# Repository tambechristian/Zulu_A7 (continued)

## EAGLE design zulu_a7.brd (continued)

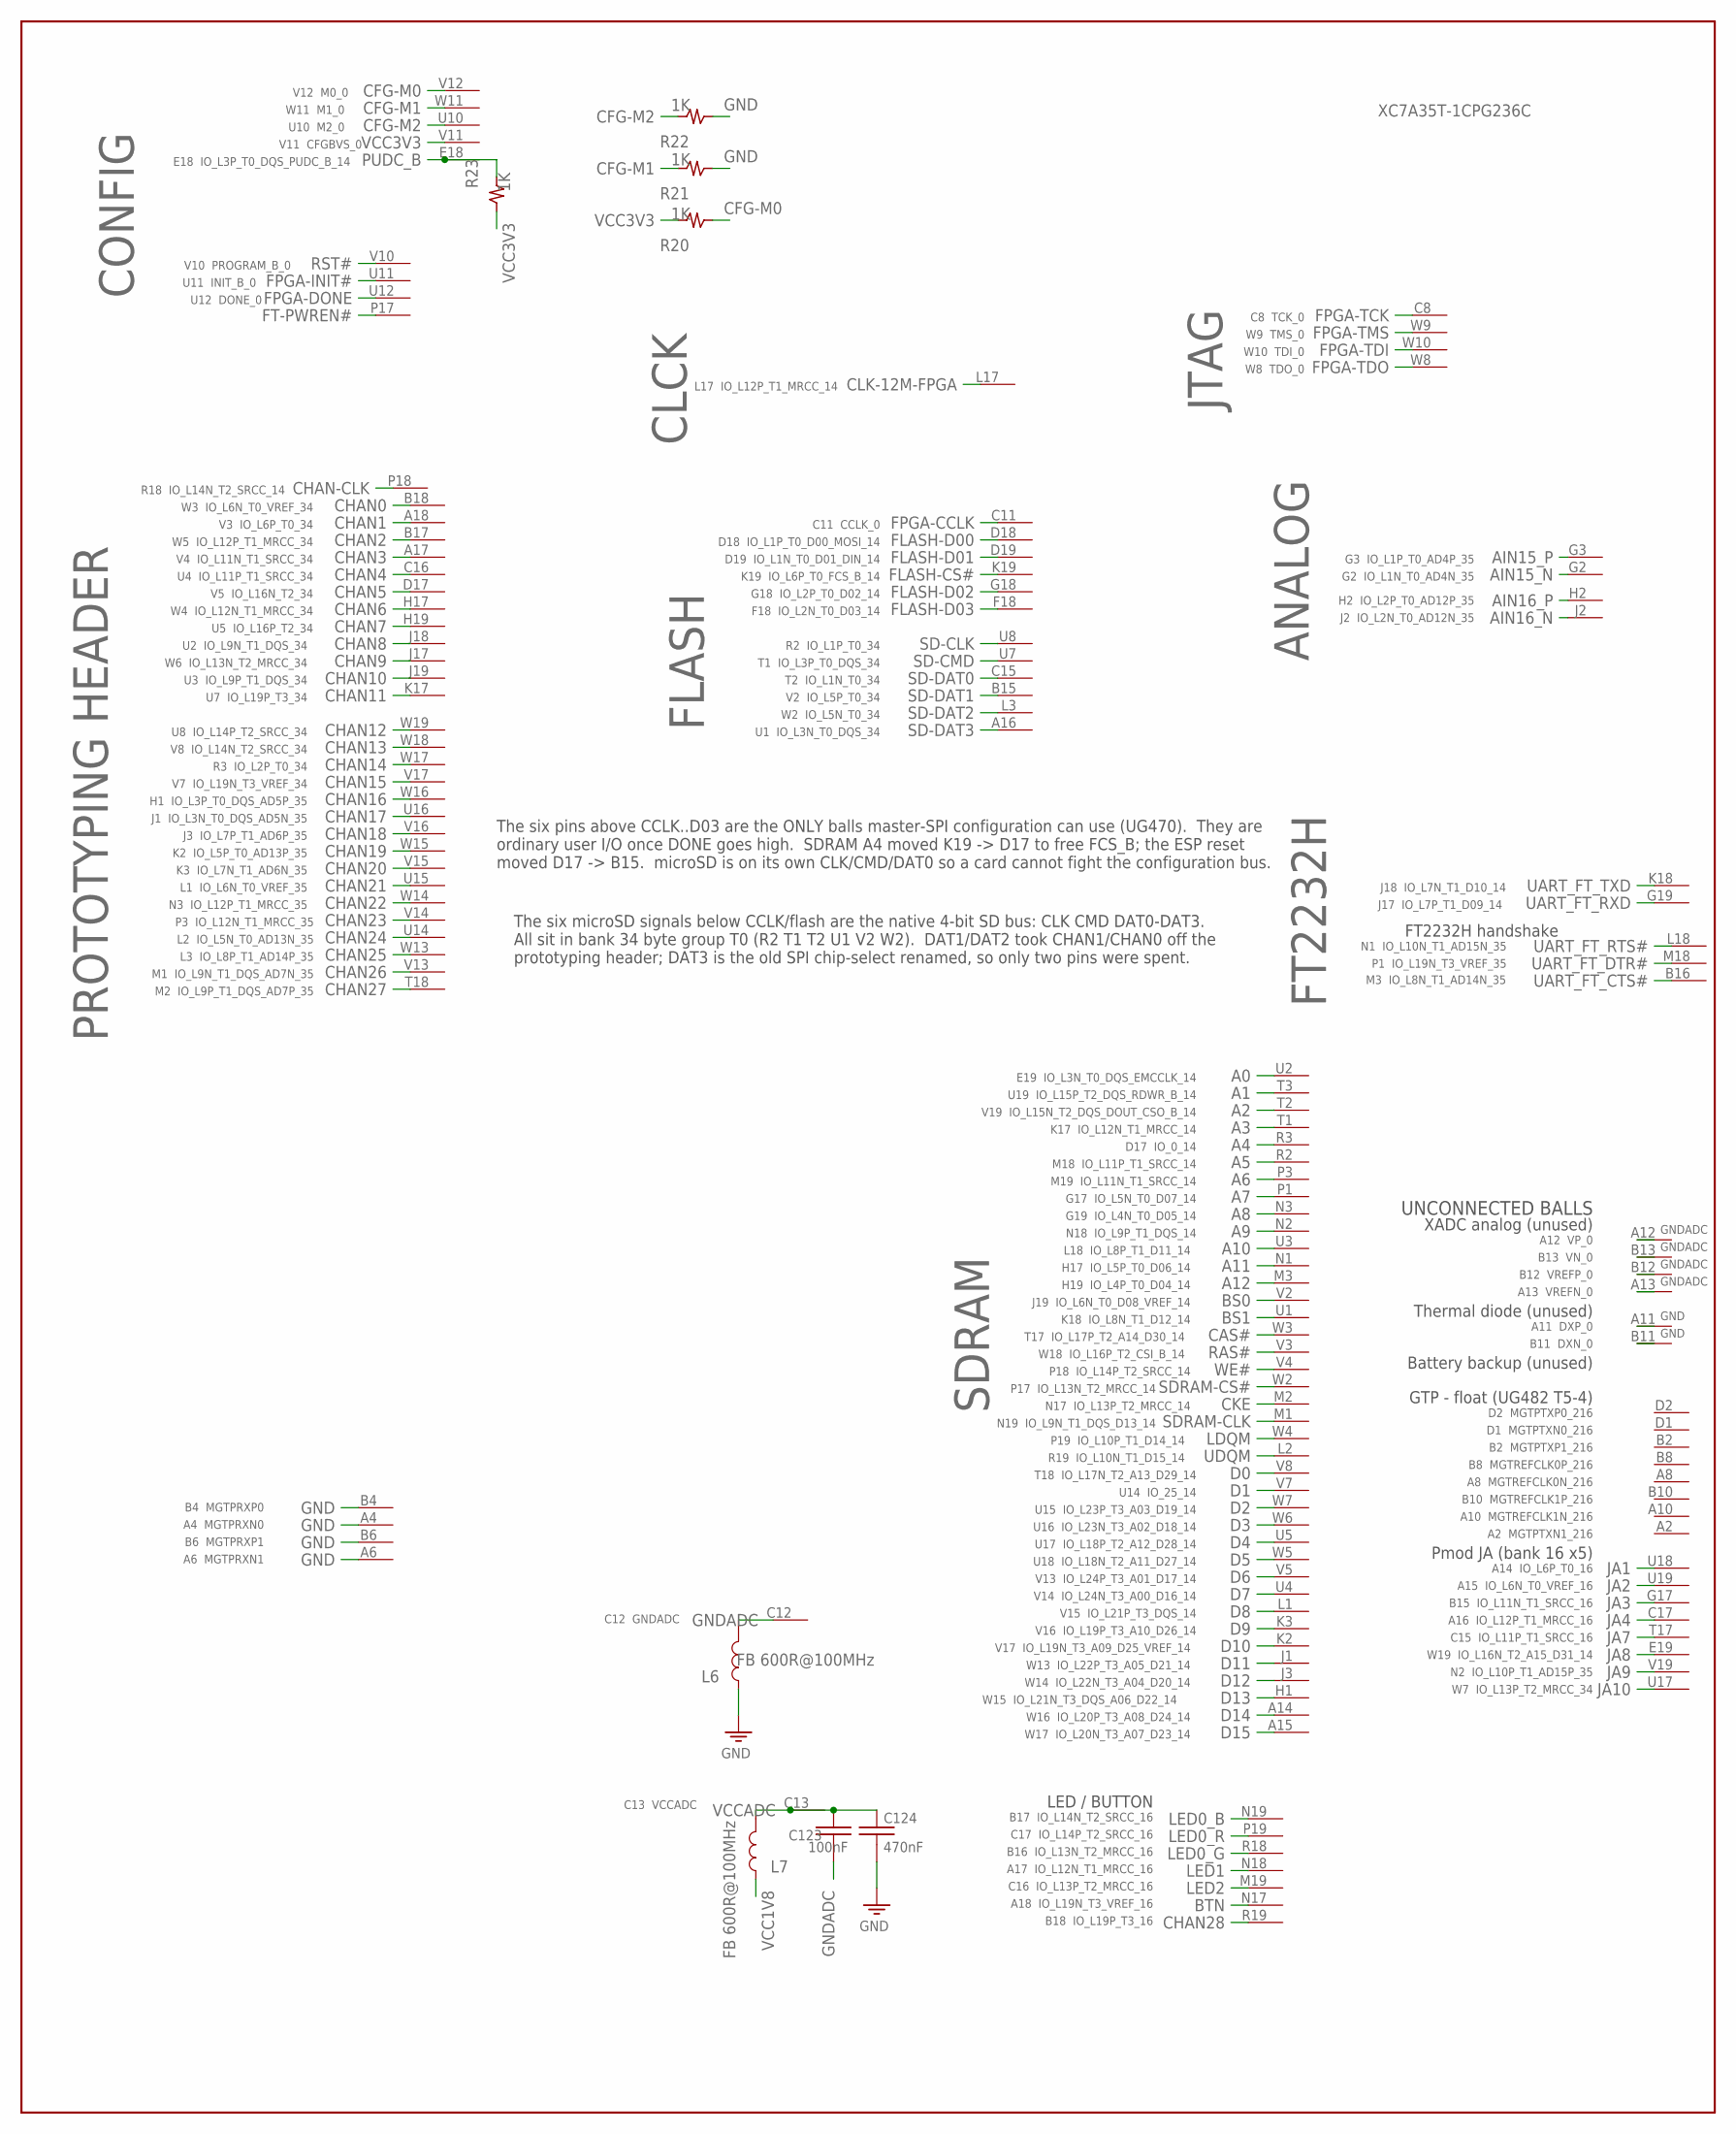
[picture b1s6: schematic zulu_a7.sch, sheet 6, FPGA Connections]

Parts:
C123: 100nF; C0402
C124: 470nF; C0402
L6, L7: FB 600R@100MHz; IND0603
R20, R21, R22, R23: 1K; R0402
U1: XC7A35T-1CPG236C; XC7A35T-CPG236

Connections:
A0: U1.U2 (1); also elsewhere on the board
A1: U1.T3 (1); also elsewhere on the board
A2: U1.T2 (1); also elsewhere on the board
A3: U1.T1 (1); also elsewhere on the board
A4: U1.R3 (1); also elsewhere on the board
A5: U1.R2 (1); also elsewhere on the board
A6: U1.P3 (1); also elsewhere on the board
A7: U1.P1 (1); also elsewhere on the board
A8: U1.N3 (1); also elsewhere on the board
A9: U1.N2 (1); also elsewhere on the board
A10: U1.U3 (1); also elsewhere on the board
A11: U1.N1 (1); also elsewhere on the board
A12: U1.M3 (1); also elsewhere on the board
AIN15_N: U1.G2 (1); also elsewhere on the board
AIN15_P: U1.G3 (1); also elsewhere on the board
AIN16_N: U1.J2 (1); also elsewhere on the board
AIN16_P: U1.H2 (1); also elsewhere on the board
BS0: U1.V2 (1); also elsewhere on the board
BS1: U1.U1 (1); also elsewhere on the board
BTN: U1.N17 (1); also elsewhere on the board
CAS#: U1.W3 (1); also elsewhere on the board
CFG-M0: R20.1, U1.V12 (1)
CFG-M1: R21.2, U1.W11 (1)
CFG-M2: R22.2, U1.U10 (1)
CHAN0: U1.B18 (1); also elsewhere on the board
CHAN1: U1.A18 (1); also elsewhere on the board
CHAN2: U1.B17 (1); also elsewhere on the board
CHAN3: U1.A17 (1); also elsewhere on the board
CHAN4: U1.C16 (1); also elsewhere on the board
CHAN5: U1.D17 (1); also elsewhere on the board
CHAN6: U1.H17 (1); also elsewhere on the board
CHAN7: U1.H19 (1); also elsewhere on the board
CHAN8: U1.J18 (1); also elsewhere on the board
CHAN9: U1.J17 (1); also elsewhere on the board
CHAN10: U1.J19 (1); also elsewhere on the board
CHAN11: U1.K17 (1); also elsewhere on the board
CHAN12: U1.W19 (1); also elsewhere on the board
CHAN13: U1.W18 (1); also elsewhere on the board
CHAN14: U1.W17 (1); also elsewhere on the board
CHAN15: U1.V17 (1); also elsewhere on the board
CHAN16: U1.W16 (1); also elsewhere on the board
CHAN17: U1.U16 (1); also elsewhere on the board
CHAN18: U1.V16 (1); also elsewhere on the board
CHAN19: U1.W15 (1); also elsewhere on the board
CHAN20: U1.V15 (1); also elsewhere on the board
CHAN21: U1.U15 (1); also elsewhere on the board
CHAN22: U1.W14 (1); also elsewhere on the board
CHAN23: U1.V14 (1); also elsewhere on the board
CHAN24: U1.U14 (1); also elsewhere on the board
CHAN25: U1.W13 (1); also elsewhere on the board
CHAN26: U1.V13 (1); also elsewhere on the board
CHAN27: U1.T18 (1); also elsewhere on the board
CHAN28: U1.R19 (1); also elsewhere on the board
CHAN-CLK: U1.P18 (1); also elsewhere on the board
CKE: U1.M2 (1); also elsewhere on the board
CLK-12M-FPGA: U1.L17 (1); also elsewhere on the board
D0: U1.V8 (1); also elsewhere on the board
D1: U1.V7 (1); also elsewhere on the board
D2: U1.W7 (1); also elsewhere on the board
D3: U1.W6 (1); also elsewhere on the board
D4: U1.U5 (1); also elsewhere on the board
D5: U1.W5 (1); also elsewhere on the board
D6: U1.V5 (1); also elsewhere on the board
D7: U1.U4 (1); also elsewhere on the board
D8: U1.L1 (1); also elsewhere on the board
D9: U1.K3 (1); also elsewhere on the board
D10: U1.K2 (1); also elsewhere on the board
D11: U1.J1 (1); also elsewhere on the board
D12: U1.J3 (1); also elsewhere on the board
D13: U1.H1 (1); also elsewhere on the board
D14: U1.A14 (1); also elsewhere on the board
D15: U1.A15 (1); also elsewhere on the board
FLASH-CS#: U1.K19 (1); also elsewhere on the board
FLASH-D00: U1.D18 (1); also elsewhere on the board
FLASH-D01: U1.D19 (1); also elsewhere on the board
FLASH-D02: U1.G18 (1); also elsewhere on the board
FLASH-D03: U1.F18 (1); also elsewhere on the board
FPGA-CCLK: U1.C11 (1); also elsewhere on the board
FPGA-DONE: U1.U12 (1); also elsewhere on the board
FPGA-INIT#: U1.U11 (1); also elsewhere on the board
FPGA-TCK: U1.C8 (1); also elsewhere on the board
FPGA-TDI: U1.W10 (1); also elsewhere on the board
FPGA-TDO: U1.W8 (1); also elsewhere on the board
FPGA-TMS: U1.W9 (1); also elsewhere on the board
FT-PWREN#: U1.P17 (1); also elsewhere on the board
GND: C124.2, L6.1, R21.1, R22.1, U1.A4 (1), U1.A6 (1), U1.A11 (1), U1.B4 (1), U1.B6 (1), U1.B11 (1); also elsewhere on the board
GNDADC: C123.2, L6.2, U1.A12 (1), U1.A13 (1), U1.B12 (1), U1.B13 (1), U1.C12 (1)
JA1: U1.U18 (1); also elsewhere on the board
JA2: U1.U19 (1); also elsewhere on the board
JA3: U1.G17 (1); also elsewhere on the board
JA4: U1.C17 (1); also elsewhere on the board
JA7: U1.T17 (1); also elsewhere on the board
JA8: U1.E19 (1); also elsewhere on the board
JA9: U1.V19 (1); also elsewhere on the board
JA10: U1.U17 (1); also elsewhere on the board
LDQM: U1.W4 (1); also elsewhere on the board
LED0_B: U1.N19 (1); also elsewhere on the board
LED0_G: U1.R18 (1); also elsewhere on the board
LED0_R: U1.P19 (1); also elsewhere on the board
LED1: U1.N18 (1); also elsewhere on the board
LED2: U1.M19 (1); also elsewhere on the board
PUDC_B: R23.2, U1.E18 (1)
RAS#: U1.V3 (1); also elsewhere on the board
RST#: U1.V10 (1); also elsewhere on the board
SD-CLK: U1.U8 (1); also elsewhere on the board
SD-CMD: U1.U7 (1); also elsewhere on the board
SD-DAT0: U1.C15 (1); also elsewhere on the board
SD-DAT1: U1.B15 (1); also elsewhere on the board
SD-DAT2: U1.L3 (1); also elsewhere on the board
SD-DAT3: U1.A16 (1); also elsewhere on the board
SDRAM-CLK: U1.M1 (1); also elsewhere on the board
SDRAM-CS#: U1.W2 (1); also elsewhere on the board
UART_FT_CTS#: U1.B16 (1); also elsewhere on the board
UART_FT_DTR#: U1.M18 (1); also elsewhere on the board
UART_FT_RTS#: U1.L18 (1); also elsewhere on the board
UART_FT_RXD: U1.G19 (1); also elsewhere on the board
UART_FT_TXD: U1.K18 (1); also elsewhere on the board
UDQM: U1.L2 (1); also elsewhere on the board
VCC1V8: L7.1; also elsewhere on the board
VCC3V3: R20.2, R23.1, U1.V11 (1); also elsewhere on the board
VCCADC: C123.1, C124.1, L7.2, U1.C13 (1)
WE#: U1.V4 (1); also elsewhere on the board

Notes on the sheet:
SDRAM
PROTOTYPING HEADER
JTAG
FLASH
CONFIG
V11 CFGBVS_0
E18 IO_L3P_T0_DQS_PUDC_B_14
C8 TCK_0
W8 TDO_0
W9 TMS_0
W10 TDI_0
U12 DONE_0
G17 IO_L5N_T0_D07_14
D19 IO_L1N_T0_D01_DIN_14
C11 CCLK_0
D18 IO_L1P_T0_D00_MOSI_14
W2 IO_L5N_T0_34
V2 IO_L5P_T0_34
W3 IO_L6N_T0_VREF_34
V3 IO_L6P_T0_34
W5 IO_L12P_T1_MRCC_34
V4 IO_L11N_T1_SRCC_34
U4 IO_L11P_T1_SRCC_34
V5 IO_L16N_T2_34
W4 IO_L12N_T1_MRCC_34
U5 IO_L16P_T2_34
U2 IO_L9N_T1_DQS_34
W6 IO_L13N_T2_MRCC_34
U3 IO_L9P_T1_DQS_34
U7 IO_L19P_T3_34
M3 IO_L8N_T1_AD14N_35
R18 IO_L14N_T2_SRCC_14
U8 IO_L14P_T2_SRCC_34
V8 IO_L14N_T2_SRCC_34
R3 IO_L2P_T0_34
V7 IO_L19N_T3_VREF_34
H1 IO_L3P_T0_DQS_AD5P_35
J1 IO_L3N_T0_DQS_AD5N_35
J3 IO_L7P_T1_AD6P_35
K2 IO_L5P_T0_AD13P_35

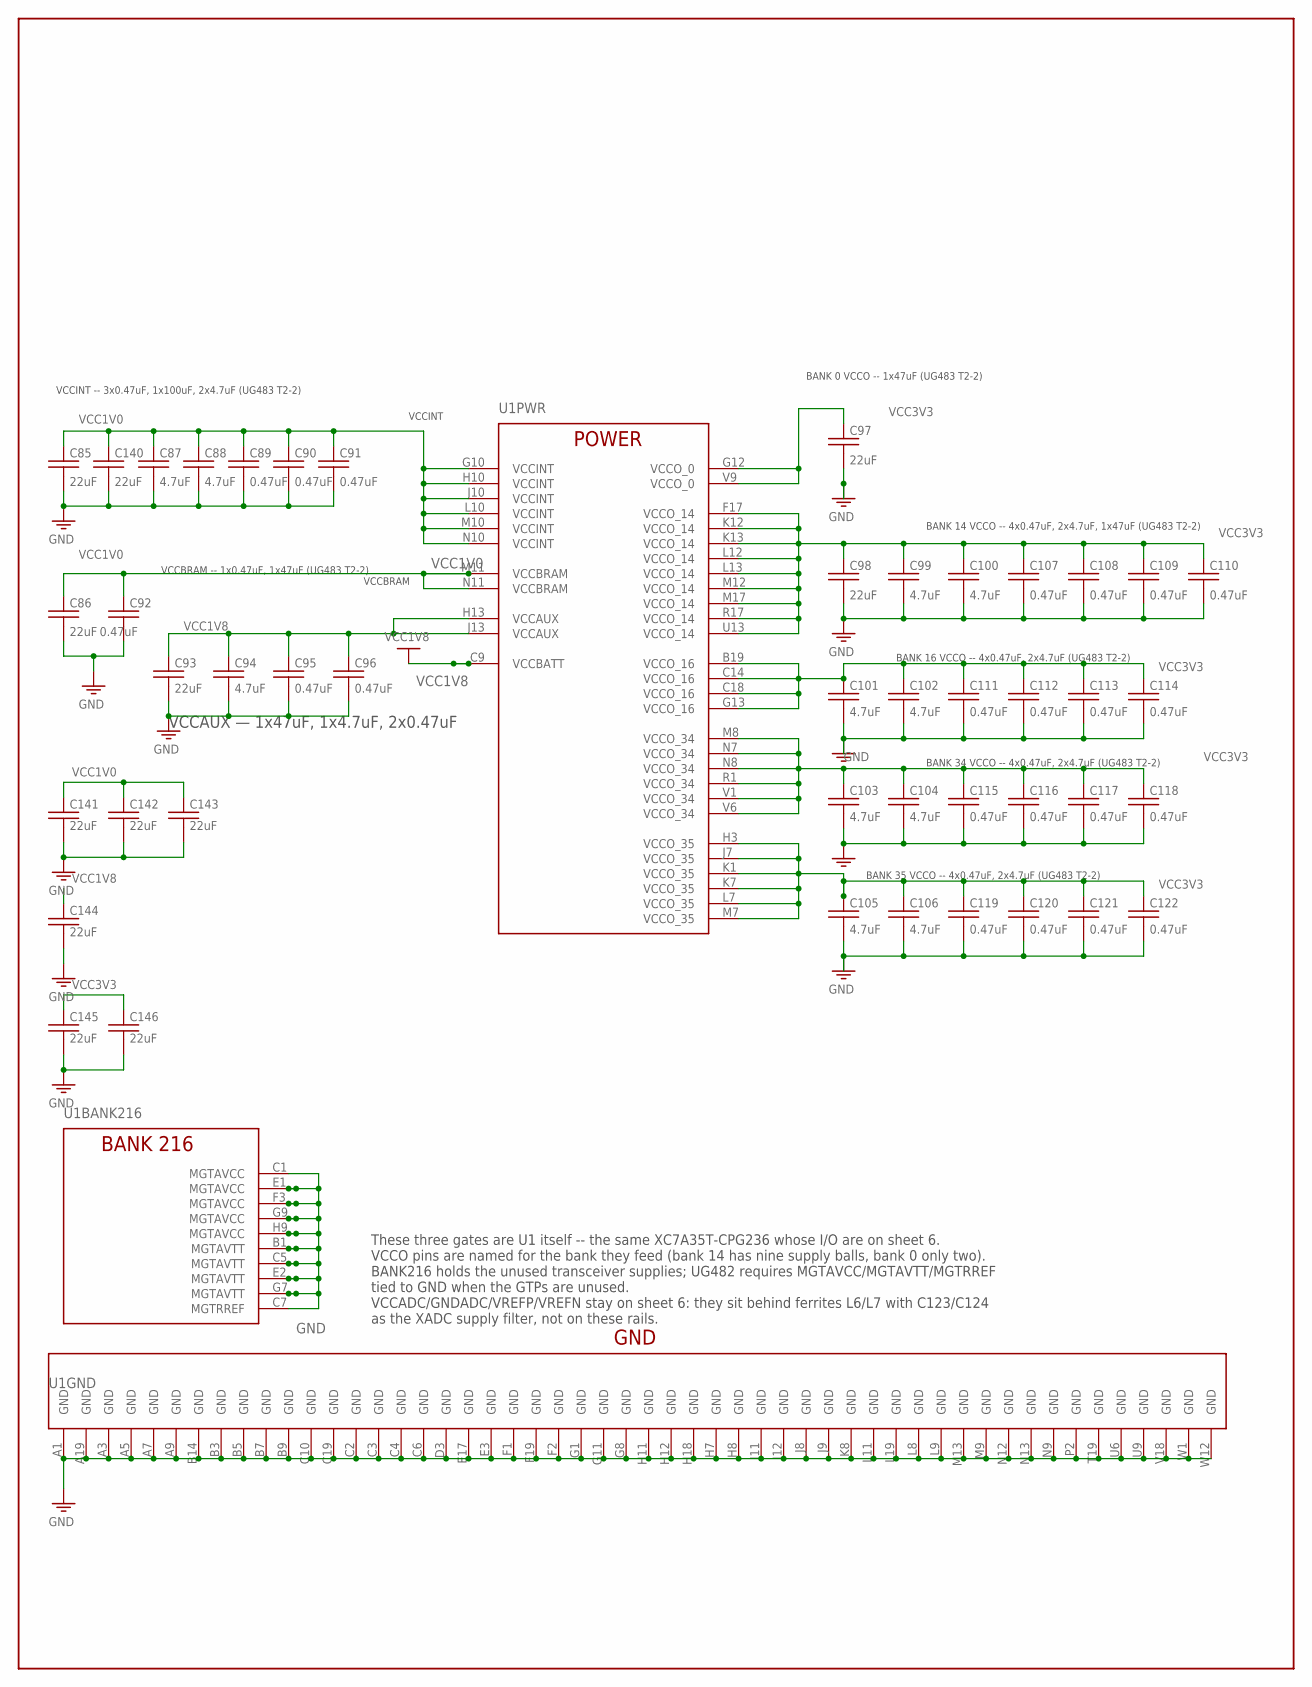
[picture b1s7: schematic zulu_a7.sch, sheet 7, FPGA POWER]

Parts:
C85, C86, C93, C97, C98, C140, C141, C142, C143, C144, C145, C146: 22uF; C0805
C87, C88, C94, C99, C100, C101, C102, C103, C104, C105, C106: 4.7uF; C0603
C89, C90, C91, C92, C95, C96, C107, C108, C109, C110, C111, C112, C113, C114, C115, C116, C117, C118, C119, C120, C121, C122: 0.47uF; C0201
U1: XC7A35T-1CPG236C; XC7A35T-CPG236

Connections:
GND: C85.2, C86.2, C87.2, C88.2, C89.2, C90.2, C91.2, C92.2, C93.2, C94.2, C95.2, C96.2, C97.2, C98.2, C99.2, C100.2, C101.2, C102.2, C103.2, C104.2, C105.2, C106.2, C107.2, C108.2, C109.2, C110.2, C111.2, C112.2, C113.2, C114.2, C115.2, C116.2, C117.2, C118.2, C119.2, C120.2, C121.2, C122.2, C140.2, C141.2, C142.2, C143.2, C144.2, C145.2, C146.2, U1.A1 (GND), U1.A3 (GND), U1.A5 (GND), U1.A7 (GND), U1.A9 (GND), U1.A19 (GND), U1.B1 (MGTAVTT), U1.B3 (GND), U1.B5 (GND), U1.B7 (GND), U1.B9 (GND), U1.B14 (GND), U1.C1 (MGTAVCC), U1.C2 (GND), U1.C3 (GND), U1.C4 (GND), U1.C5 (MGTAVTT), U1.C6 (GND), U1.C7 (MGTRREF), U1.C10 (GND), U1.C19 (GND), U1.D3 (GND), U1.E1 (MGTAVCC), U1.E2 (MGTAVTT), U1.E3 (GND), U1.E17 (GND), U1.F1 (GND), U1.F2 (GND), U1.F3 (MGTAVCC), U1.F19 (GND), U1.G1 (GND), U1.G7 (MGTAVTT), U1.G8 (GND), U1.G9 (MGTAVCC), U1.G11 (GND), U1.H7 (GND), U1.H8 (GND), U1.H9 (MGTAVCC), U1.H11 (GND), U1.H12 (GND), U1.H18 (GND), U1.J8 (GND), U1.J9 (GND), U1.J11 (GND), U1.J12 (GND), U1.K8 (GND), U1.L8 (GND), U1.L9 (GND), U1.L11 (GND), U1.L19 (GND), U1.M9 (GND), U1.M13 (GND), U1.N9 (GND), U1.N12 (GND), U1.N13 (GND), U1.P2 (GND), U1.T19 (GND), U1.U6 (GND), U1.U9 (GND), U1.V18 (GND), U1.W1 (GND), U1.W12 (GND); also elsewhere on the board
VCC1V0: C85.1, C86.1, C87.1, C88.1, C89.1, C90.1, C91.1, C92.1, C140.1, C141.1, C142.1, C143.1, U1.G10 (VCCINT), U1.H10 (VCCINT), U1.J10 (VCCINT), U1.L10 (VCCINT), U1.M10 (VCCINT), U1.M11 (VCCBRAM), U1.N10 (VCCINT), U1.N11 (VCCBRAM); also elsewhere on the board
VCC1V8: C93.1, C94.1, C95.1, C96.1, C144.1, U1.C9 (VCCBATT), U1.H13 (VCCAUX), U1.J13 (VCCAUX); also elsewhere on the board
VCC3V3: C97.1, C98.1, C99.1, C100.1, C101.1, C102.1, C103.1, C104.1, C105.1, C106.1, C107.1, C108.1, C109.1, C110.1, C111.1, C112.1, C113.1, C114.1, C115.1, C116.1, C117.1, C118.1, C119.1, C120.1, C121.1, C122.1, C145.1, C146.1, U1.B19 (VCCO_16), U1.C14 (VCCO_16), U1.C18 (VCCO_16), U1.F17 (VCCO_14), U1.G12 (VCCO_0), U1.G13 (VCCO_16), U1.H3 (VCCO_35), U1.J7 (VCCO_35), U1.K1 (VCCO_35), U1.K7 (VCCO_35), U1.K12 (VCCO_14), U1.K13 (VCCO_14), U1.L7 (VCCO_35), U1.L12 (VCCO_14), U1.L13 (VCCO_14), U1.M7 (VCCO_35), U1.M8 (VCCO_34), U1.M12 (VCCO_14), U1.M17 (VCCO_14), U1.N7 (VCCO_34), U1.N8 (VCCO_34), U1.R1 (VCCO_34), U1.R17 (VCCO_14), U1.U13 (VCCO_14), U1.V1 (VCCO_34), U1.V6 (VCCO_34), U1.V9 (VCCO_0); also elsewhere on the board

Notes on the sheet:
VCCAUX — 1x47uF, 1x4.7uF, 2x0.47uF
These three gates are U1 itself -- the same XC7A35T-CPG236 whose I/O are on sheet 6. VCCO pins are named for the bank they feed (bank 14 has nine supply balls, bank 0 only two). BANK216 holds the unused transceiver supplies; UG482 requires MGTAVCC/MGTAVTT/MGTRREF tied to GND when the GTPs are unuse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
BANK 0 VCCO -- 1x47uF (UG483 T2-2)
BANK 14 VCCO -- 4x0.47uF, 2x4.7uF, 1x47uF (UG483 T2-2)
BANK 16 VCCO -- 4x0.47uF, 2x4.7uF (UG483 T2-2)
BANK 34 VCCO -- 4x0.47uF, 2x4.7uF (UG483 T2-2)
BANK 35 VCCO -- 4x0.47uF, 2x4.7uF (UG483 T2-2)
VCCINT
VCCBRAM
VCCINT -- 3x0.47uF, 1x100uF, 2x4.7uF (UG483 T2-2)
VCCBRAM -- 1x0.47uF, 1x47uF (UG483 T2-2)

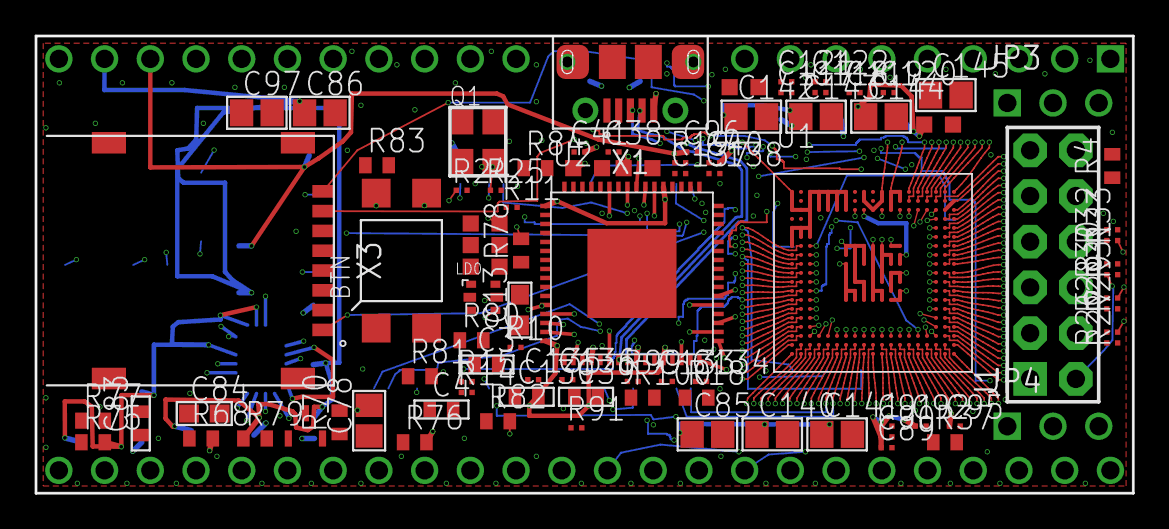
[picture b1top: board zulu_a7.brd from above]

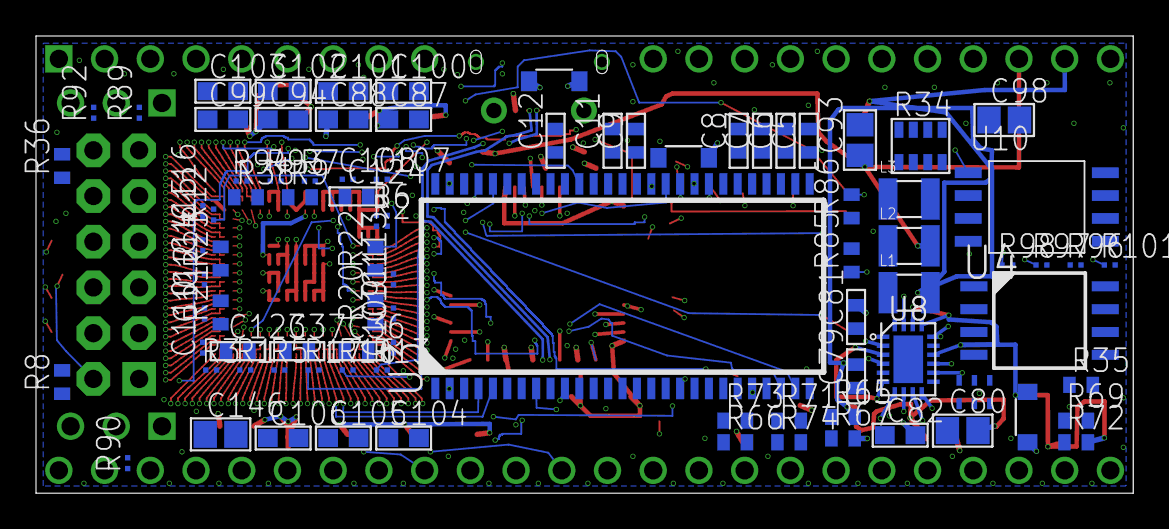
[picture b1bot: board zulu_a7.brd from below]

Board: 6 copper layers, 61.0 x 25.4 mm, 183 parts (89 on the bottom side), 175 nets.

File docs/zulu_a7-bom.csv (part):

Item,Qty,Refdes,Value,Package,Manufacturer,MANF#,Spec,Fitted,Note
1,1,J1,Pmod 2x6,2X06,Sullins,PPTC062LFBN-RC,"2x6 female header, 2.54 mm pitch, through-hole, 12 way -- Pmod host socket",yes,"A SOCKET, NOT PINS, AND THE LIBRARY NAME DISAGREES WITH THAT. The package is called PIN HEADER 2x6 and the deviceset PINHD-2X6, which is inherited naming, but on a Digilent Pmod the HOST carries the female socket and the peripheral module carries the male pins that plug into it. Cmod A7 is the same. Order male pins off that library name and no Pmod will mate. The footprint is 12 plated holes on 2."
2,1,Q1,12MHz 25ppm (FPGA + FT2232HQ),32X25,Abracon,ASEM1-12.000MHZ-LC-T,"12.000 MHz CMOS oscillator, 3.3V, 25 ppm, 3.2 x 2.5 mm 4-pad, pin 1 enable or NC, pin 3 output",yes,"ACTIVE OSCILLATOR, NOT A CRYSTAL -- the schematic settles it: pin 2 to GND, pin 4 to VCC3V3, pin 3 out into R24 and R25, and pin 1 tied to VCC3V3, which is a 4-pad XO with its enable held high. A crystal would have two pads and load capacitors. THE FREQUENCY IS NOT A CHOICE: the FT2232H wants 12 MHz for its USB PLL, so that was fixed before anything else. 25 ppm is the value already recorded and i"
3,1,R34,4.7K,742C083,CTS,742C083472JTR,"4-element isolated resistor array, 4.7k, 5 percent or better, 742C083 8-pin convex land",yes,"The microSD DAT0-3 pull-ups, all four elements used -- which is what an array is actually for, unlike R1, R2 and R4, which used 2, 3 and 6 of theirs and were split into discretes. This one stays an array. 4.7k is the conventional value for SD data lines and it was already chosen; only the part number was missing. 5 percent is ample for a pull-up, so this is a J part where the discrete resistors on"
4,22,C89 C90 C91 C92 C95 C96 C107 C108 C109 C110 C111 C112 C113 C114 C115 C116 C117 C118 C119 C120 C121 C122,0.47uF,C0201,Murata,GRM033R60J474KE15D,"X5R 6.3V +-10%, 0.30 mm max",yes,"0402 -> 0201 to cut ESL, following Cmod A7. THE VOLTAGE RATING DROPS 16V to 6.3V and that costs real capacitance: on VCC3V3 a 6.3V 0201 sits at 52 percent of rating and DC bias typically removes 60-75 percent of it, against 15-25 percent for the 16V 0402 it replaces. The BOM value is unchanged, so validate.py's UG483 count still passes -- it counts nominal values and cannot see bias derating. Effe"
5,8,C40 C41 C133 C134 C135 C136 C137 C138,0.1uF / 100nF,C0201,Murata,GRM033R61A104KE15D,"X5R 10V +-10%, 0.30 mm max",yes,"0402 -> 0201 on U2's support. The DIELECTRIC AND VOLTAGE BOTH CHANGE: X7R 16V becomes X5R 10V, because 0201 at this capacitance is an X5R part. X5R narrows the temperature range to -55..+85 C from X7R's +125, which suits this board but is not a like-for-like swap. At 0.1 uF the DC bias derating is mild, unlike the 0.47 uF on sheet 7. Confirm the MPN suffix against Murata's data before ordering."
6,1,C38,0.01uF,C0201,Murata,GRM033R71E103KE14D,"X7R 25V +-10%, 0.30 mm max",yes,"0402 -> 0201 on U2's support. 50V drops to 25V, which is still far over what a 3.3V rail needs -- the 50V part was over-specified. Confirm the MPN suffix before ordering."
7,3,C79 C81 C83,20pF,C0402,Murata,GRM1555C1H200JA01D,"C0G 50V +-5%, 0.50 mm max -- C0G for the feedback feedforward",yes,
8,2,C39 C139,3.3uF,C0402,Murata,GRM155R60J335ME15D,"X5R 6.3V +-20%, 0.50 mm max -- FT2232H VCORE, DS_FT2232H asks for 3.3uF",yes,
9,1,C124,470nF,C0402,Murata,GRM155R61C474KA88D,"X5R 16V +-10%, 0.50 mm max -- same part as the 0.47uF line",yes,
10,10,C3 C4 C5 C6 C7 C8 C9 C11 C12 C123,0.1uF / 100nF,C0402,Murata,GRM155R71C104KA88D,"X7R 16V +-10%, 0.50 mm max",yes,
11,2,C36 C37,1nF,C0402,Murata,GRM155R71H102KA01D,"X7R 50V +-10%, 0.50 mm max",yes,
12,3,C13 C82 C84,10uF,C0603,Murata,GRM188R60J106ME47D,"X5R 6.3V +-20%, 0.90 mm max",yes,
13,11,C87 C88 C94 C99 C100 C101 C102 C103 C104 C105 C106,4.7uF,C0603,Murata,GRM188R61A475KE15D,"X5R 10V +-10%, 0.90 mm max",yes,
14,14,C78 C80 C85 C86 C93 C97 C98 C140 C141 C142 C143 C144 C145 C146,22uF / 22uF 10V,C0805,Murata,GRM21BR61A226ME44L,"X5R 10V +-20%, 1.45 mm max -- LTC3569 CIN on VU (5V USB)",yes,
15,1,X3,,DM3AT-SF-PEJM5,Hirose,DM3AT-SF-PEJM5,,yes,
16,1,U2,FT2232HQ USB-UART/JTAG Bridge,FT2232HQ-QFN64,FTDI,FT2232HQ-REEL,,yes,
17,4,L4 L5 L6 L7,FB 600R@100MHz,IND0603,Murata,BLM18PG601SN1D,"600 ohm at 100MHz, 1.5A, 0.90 mm max",yes,
18,1,L1,1.5uH,IND2520,Murata,DFE252010P-1R5M=P2,"1.5uH +-20%, Idc >=1.8A REQUIRED, 1.00 mm max -- SW1, 1.2A buck",yes,
19,1,L3,2.2uH,IND2520,Murata,DFE252010P-2R2M=P2,"2.2uH +-20%, Idc >=0.9A REQUIRED, 1.00 mm max -- SW3, 600mA buck",yes,
20,1,L2,3.3uH,IND2520,Murata,DFE252010P-3R3M=P2,"3.3uH +-20%, Idc >=0.9A REQUIRED, 1.00 mm max -- SW2, 600mA buck",yes,
21,1,LD5,green,LED0603,Lite-On,LTST-C191KGKT,"green indicator, 0603, Vf 2.1V max at 2mA",yes,"Power-good indicator: VCC3V3 to LD5 to R78 680R to Q2 drain to GND. SELECTED FROM THE CIRCUIT, not recovered -- the part carried no value and no number. THE RESISTOR ALREADY CHOSE THE COLOUR: 680R off 3.3 V passes (3.3 - Vf)/680, which is 1.9 mA for a green LED or 2.1 for a red, but only 0.6 mA for a blue or white one, too dim to read. So it is a green or red part, and green is the convention for "
22,2,LD1 LD2,red,LED0603,Lite-On,LTST-C191KRKT,"red indicator, 0603, Vf 2.1V max at 4mA",yes,"User status LED, driven straight off an FPGA pin through R83 at 330R: (3.3 - Vf)/330 is 3.9 mA green, 4.2 red, 3.6 yellow, and 1.2 mA blue or white. Any of the first three is comfortable and well inside an LVCMOS33 pin's 12 mA. RED IS A PREFERENCE, NOT A CONSTRAINT -- the circuit takes green just as happily. It is red so that the two user LEDs read differently from LD5, which is green and means po"
23,1,U8,LTC3569EUDC#TRPBF,LTC3569-QFN20,Analog Devices,LTC3569EUDC#TRPBF,,yes,
24,1,X1,Molex 105017-0001 Micro-USB-B,MOLEX-105017-0001,Molex,105017-0001,,yes,
25,1,BTN,PTA-142,PTA-142,,PTA-142,"tactile switch, SMD gull-wing, 4.5 x 4.5 mm, 130 gf, DC12V 50 mA, 50000 cycles",yes,"PTA-142, from the catalogue page in Datasheet/pta142-112.pdf. THE PART NUMBER IS COMPLETE AS IT STANDS: the sheet lists one operating force (130 gf +-30), one stem colour (black) and no ordering suffix table, so there is nothing to append. It is the SMD reflow member of the family -- PTA-112 and PTA-113 are through-hole, PTA-143 is the SMD with a ground terminal. Rated DC12V 50 mA, 100 mOhm contac"
26,10,R19 R89 R90 R91 R92 R93 R94 R96 R97 R98,10K / 10k,R0201,Yageo,RC0201FR-0710KL,"thick film +-1%, 1/20W, 0201",yes,
27,2,R12 R16,140,R0201,Yageo,RC0201FR-07140RL,"thick film +-1%, 1/20W, 0201",yes,
28,2,R11 R15,1K,R0201,Yageo,RC0201FR-071KL,"thick film +-1%, 1/20W, 0201",yes,
29,8,R26 R27 R28 R29 R30 R31 R32 R33,200,R0201,Yageo,RC0201FR-07200RL,"thick film +-1%, 1/20W, 0201",yes,
30,1,R101,2.21k,R0201,Yageo,RC0201FR-072K21L,"thick film +-1%, 1/20W, 0201",yes,
31,2,R10 R14,2.32K,R0201,Yageo,RC0201FR-072K32L,"thick film +-1%, 1/20W, 0201",yes,
32,2,R24 R25,33,R0201,Yageo,RC0201FR-0733RL,"thick film +-1%, 1/20W, 0201",yes,
33,6,R1 R2 R3 R6 R7 R99,4.7K / 4.7k,R0201,Yageo,RC0201FR-074K7L,"thick film +-1%, 1/20W, 0201",yes,
34,1,R5,5.1K,R0201,Yageo,RC0201FR-075K1L,"thick film +-1%, 1/20W, 0201",yes,
35,2,R13 R17,845,R0201,Yageo,RC0201FR-07845RL,"thick film +-1%, 1/20W, 0201",yes,
36,4,R74 R75 R76 R77,100K,R0402,Yageo,RC0402FR-07100KL,"thick film +-1%, 1/16W, 0402",yes,
37,6,R4 R8 R9 R36 R37 R38,100,R0402,Yageo,RC0402FR-07100RL,"thick film +-1%, 1/16W, 0402",yes,
38,3,R70 R85 R86,10K / 10K 1%,R0402,Yageo,RC0402FR-0710KL,"thick film +-1%, 1/16W, 0402",yes,
39,2,R66 R69,120K 1%,R0402,Yageo,RC0402FR-07120KL,"thick film +-1%, 1/16W, 0402",yes,
40,1,R18,12K 1%,R0402,Yageo,RC0402FR-0712KL,"thick film +-1%, 1/16W, 0402",yes,"Stays 0402 deliberately. Power is trivial (0.9 mW) and 1 percent is 1 percent at any size, but this is the FT2232's RREF -- it sets the USB transceiver bias current. There is no space pressure on this board any more, so there is nothing to gain against a part whose drift shows up as USB signal quality."
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
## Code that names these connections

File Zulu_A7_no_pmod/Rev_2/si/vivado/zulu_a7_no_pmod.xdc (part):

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set_property -dict {PACKAGE_PIN N2   IOSTANDARD LVCMOS33} [get_ports {A9}]  ;# A9  bank 35  IO_L10P_T1_AD15P_35
set_property -dict {PACKAGE_PIN V2   IOSTANDARD LVCMOS33} [get_ports {BS0}]  ;# BS0  bank 34  IO_L5P_T0_34
set_property -dict {PACKAGE_PIN U1   IOSTANDARD LVCMOS33} [get_ports {BS1}]  ;# BS1  bank 34  IO_L3N_T0_DQS_34
set_property -dict {PACKAGE_PIN N19  IOSTANDARD LVCMOS33} [get_ports {BTN}]  ;# BTN  bank 14  IO_L9N_T1_DQS_D13_14
set_property -dict {PACKAGE_PIN W3   IOSTANDARD LVCMOS33} [get_ports {CAS_N}]  ;# CAS#  bank 34  IO_L6N_T0_VREF_34
set_property -dict {PACKAGE_PIN B18  IOSTANDARD LVCMOS33} [get_ports {CHAN0}]  ;# CHAN0  bank 16  IO_L19P_T3_16
set_property -dict {PACKAGE_PIN A18  IOSTANDARD LVCMOS33} [get_ports {CHAN1}]  ;# CHAN1  bank 16  IO_L19N_T3_VREF_16
set_property -dict {PACKAGE_PIN J19  IOSTANDARD LVCMOS33} [get_ports {CHAN10}]  ;# CHAN10  bank 14  IO_L6N_T0_D08_VREF_14
set_property -dict {PACKAGE_PIN K18  IOSTANDARD LVCMOS33} [get_ports {CHAN11}]  ;# CHAN11  bank 14  IO_L8N_T1_D12_14
set_property -dict {PACKAGE_PIN E19  IOSTANDARD LVCMOS33} [get_ports {CHAN12}]  ;# CHAN12  bank 14  IO_L3N_T0_DQS_EMCCLK_14
set_property -dict {PACKAGE_PIN H19  IOSTANDARD LVCMOS33} [get_ports {CHAN13}]  ;# CHAN13  bank 14  IO_L4P_T0_D04_14
set_property -dict {PACKAGE_PIN W17  IOSTANDARD LVCMOS33} [get_ports {CHAN14}]  ;# CHAN14  bank 14  IO_L20N_T3_A07_D23_14
set_property -dict {PACKAGE_PIN V17  IOSTANDARD LVCMOS33} [get_ports {CHAN15}]  ;# CHAN15  bank 14  IO_L19N_T3_A09_D25_VREF_14
set_property -dict {PACKAGE_PIN W16  IOSTANDARD LVCMOS33} [get_ports {CHAN16}]  ;# CHAN16  bank 14  IO_L20P_T3_A08_D24_14
set_property -dict {PACKAGE_PIN U16  IOSTANDARD LVCMOS33} [get_ports {CHAN17}]  ;# CHAN17  bank 14  IO_L23N_T3_A02_D18_14
set_property -dict {PACKAGE_PIN V16  IOSTANDARD LVCMOS33} [get_ports {CHAN18}]  ;# CHAN18  bank 14  IO_L19P_T3_A10_D26_14
set_property -dict {PACKAGE_PIN W15  IOSTANDARD LVCMOS33} [get_ports {CHAN19}]  ;# CHAN19  bank 14  IO_L21N_T3_DQS_A06_D22_14
set_property -dict {PACKAGE_PIN B17  IOSTANDARD LVCMOS33} [get_ports {CHAN2}]  ;# CHAN2  bank 16  IO_L14N_T2_SRCC_16
set_property -dict {PACKAGE_PIN V15  IOSTANDARD LVCMOS33} [get_ports {CHAN20}]  ;# CHAN20  bank 14  IO_L21P_T3_DQS_14
set_property -dict {PACKAGE_PIN U15  IOSTANDARD LVCMOS33} [get_ports {CHAN21}]  ;# CHAN21  bank 14  IO_L23P_T3_A03_D19_14
set_property -dict {PACKAGE_PIN W14  IOSTANDARD LVCMOS33} [get_ports {CHAN22}]  ;# CHAN22  bank 14  IO_L22N_T3_A04_D20_14
set_property -dict {PACKAGE_PIN V14  IOSTANDARD LVCMOS33} [get_ports {CHAN23}]  ;# CHAN23  bank 14  IO_L24N_T3_A00_D16_14
set_property -dict {PACKAGE_PIN U14  IOSTANDARD LVCMOS33} [get_ports {CHAN24}]  ;# CHAN24  bank 14  IO_25_14
set_property -dict {PACKAGE_PIN W13  IOSTANDARD LVCMOS33} [get_ports {CHAN25}]  ;# CHAN25  bank 14  IO_L22P_T3_A05_D21_14
set_property -dict {PACKAGE_PIN V13  IOSTANDARD LVCMOS33} [get_ports {CHAN26}]  ;# CHAN26  bank 14  IO_L24P_T3_A01_D17_14
set_property -dict {PACKAGE_PIN T18  IOSTANDARD LVCMOS33} [get_ports {CHAN27}]  ;# CHAN27  bank 14  IO_L17N_T2_A13_D29_14
set_property -dict {PACKAGE_PIN T17  IOSTANDARD LVCMOS33} [get_ports {CHAN28}]  ;# CHAN28  bank 14  IO_L17P_T2_A14_D30_14
set_property -dict {PACKAGE_PIN A17  IOSTANDARD LVCMOS33} [get_ports {CHAN3}]  ;# CHAN3  bank 16  IO_L12N_T1_MRCC_16
set_property -dict {PACKAGE_PIN C16  IOSTANDARD LVCMOS33} [get_ports {CHAN4}]  ;# CHAN4  bank 16  IO_L13P_T2_MRCC_16
set_property -dict {PACKAGE_PIN D17  IOSTANDARD LVCMOS33} [get_ports {CHAN5}]  ;# CHAN5  bank 14  IO_0_14
set_property -dict {PACKAGE_PIN H17  IOSTANDARD LVCMOS33} [get_ports {CHAN6}]  ;# CHAN6  bank 14  IO_L5P_T0_D06_14
set_property -dict {PACKAGE_PIN G17  IOSTANDARD LVCMOS33} [get_ports {CHAN7}]  ;# CHAN7  bank 14  IO_L5N_T0_D07_14
set_property -dict {PACKAGE_PIN J18  IOSTANDARD LVCMOS33} [get_ports {CHAN8}]  ;# CHAN8  bank 14  IO_L7N_T1_D10_14
set_property -dict {PACKAGE_PIN J17  IOSTANDARD LVCMOS33} [get_ports {CHAN9}]  ;# CHAN9  bank 14  IO_L7P_T1_D09_14
set_property -dict {PACKAGE_PIN P18  IOSTANDARD LVCMOS33} [get_ports {CHAN_CLK}]  ;# CHAN-CLK  bank 14  IO_L14P_T2_SRCC_14
set_property -dict {PACKAGE_PIN M2   IOSTANDARD LVCMOS33} [get_ports {CKE}]  ;# CKE  bank 35  IO_L9P_T1_DQS_AD7P_35
set_property -dict {PACKAGE_PIN L17  IOSTANDARD LVCMOS33} [get_ports {CLK_12M_FPGA}]  ;# CLK-12M-FPGA  bank 14  IO_L12P_T1_MRCC_14
set_property -dict {PACKAGE_PIN V8   IOSTANDARD LVCMOS33} [get_ports {D0}]  ;# D0  bank 34  IO_L14N_T2_SRCC_34
set_property -dict {PACKAGE_PIN V7   IOSTANDARD LVCMOS33} [get_ports {D1}]  ;# D1  bank 34  IO_L19N_T3_VREF_34
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set_property -dict {PACKAGE_PIN G18  IOSTANDARD LVCMOS33} [get_ports {FLASH_D02}]  ;# FLASH-D02  bank 14  IO_L2P_T0_D02_14
set_property -dict {PACKAGE_PIN F18  IOSTANDARD LVCMOS33} [get_ports {FLASH_D03}]  ;# FLASH-D03  bank 14  IO_L2N_T0_D03_14
set_property -dict {PACKAGE_PIN P19  IOSTANDARD LVCMOS33} [get_ports {FT_PWREN_N}]  ;# FT-PWREN#  bank 14  IO_L10P_T1_D14_14
set_property -dict {PACKAGE_PIN W4   IOSTANDARD LVCMOS33} [get_ports {LDQM}]  ;# LDQM  bank 34  IO_L12N_T1_MRCC_34
set_property -dict {PACKAGE_PIN N17  IOSTANDARD LVCMOS33} [get_ports {LED0_B}]  ;# LED0_B  bank 14  IO_L13P_T2_MRCC_14
set_property -dict {PACKAGE_PIN R18  IOSTANDARD LVCMOS33} [get_ports {LED0_G}]  ;# LED0_G  bank 14  IO_L14N_T2_SRCC_14
set_property -dict {PACKAGE_PIN P17  IOSTANDARD LVCMOS33} [get_ports {LED0_R}]  ;# LED0_R  bank 14  IO_L13N_T2_MRCC_14
set_property -dict {PACKAGE_PIN N18  IOSTANDARD LVCMOS33} [get_ports {LED1}]  ;# LED1  bank 14  IO_L9P_T1_DQS_14
set_property -dict {PACKAGE_PIN M19  IOSTANDARD LVCMOS33} [get_ports {LED2}]  ;# LED2  bank 14  IO_L11N_T1_SRCC_14
set_property -dict {PACKAGE_PIN V3   IOSTANDARD LVCMOS33} [get_ports {RAS_N}]  ;# RAS#  bank 34  IO_L6P_T0_34
set_property -dict {PACKAGE_PIN M1   IOSTANDARD LVCMOS33} [get_ports {SDRAM_CLK}]  ;# SDRAM-CLK  bank 35  IO_L9N_T1_DQS_AD7N_35
set_property -dict {PACKAGE_PIN W2   IOSTANDARD LVCMOS33} [get_ports {SDRAM_CS_N}]  ;# SDRAM-CS#  bank 34  IO_L5N_T0_34
set_property -dict {PACKAGE_PIN U8   IOSTANDARD LVCMOS33} [get_ports {SD_CLK}]  ;# SD-CLK  bank 34  IO_L14P_T2_SRCC_34
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set_property -dict {PACKAGE_PIN B15  IOSTANDARD LVCMOS33} [get_ports {SD_DAT1}]  ;# SD-DAT1  bank 16  IO_L11N_T1_SRCC_16
set_property -dict {PACKAGE_PIN L3   IOSTANDARD LVCMOS33} [get_ports {SD_DAT2}]  ;# SD-DAT2  bank 35  IO_L8P_T1_AD14P_35
set_property -dict {PACKAGE_PIN A16  IOSTANDARD LVCMOS33} [get_ports {SD_DAT3}]  ;# SD-DAT3  bank 16  IO_L12P_T1_MRCC_16
set_property -dict {PACKAGE_PIN B16  IOSTANDARD LVCMOS33} [get_ports {UART_FT_CTS_N}]  ;# UART_FT_CTS#  bank 16  IO_L13N_T2_MRCC_16
set_property -dict {PACKAGE_PIN M18  IOSTANDARD LVCMOS33} [get_ports {UART_FT_DTR_N}]  ;# UART_FT_DTR#  bank 14  IO_L11P_T1_SRCC_14
set_property -dict {PACKAGE_PIN L18  IOSTANDARD LVCMOS33} [get_ports {UART_FT_RTS_N}]  ;# UART_FT_RTS#  bank 14  IO_L8P_T1_D11_14
set_property -dict {PACKAGE_PIN G19  IOSTANDARD LVCMOS33} [get_ports {UART_FT_RXD}]  ;# UART_FT_RXD  bank 14  IO_L4N_T0_D05_14
set_property -dict {PACKAGE_PIN K17  IOSTANDARD LVCMOS33} [get_ports {UART_FT_TXD}]  ;# UART_FT_TXD  bank 14  IO_L12N_T1_MRCC_14
set_property -dict {PACKAGE_PIN L2   IOSTANDARD LVCMOS33} [get_ports {UDQM}]  ;# UDQM  bank 35  IO_L5N_T0_AD13N_35
set_property -dict {PACKAGE_PIN V4   IOSTANDARD LVCMOS33} [get_ports {WE_N}]  ;# WE#  bank 34  IO_L11N_T1_SRCC_34

# ---- SDRAM bus drive strength, 2026-09-15 -----------------------------------------------
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
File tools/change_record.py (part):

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        ("", "Triple synchronous buck. Replaces the two LDOs rev1 proposed and the two the original board had &mdash; one part now makes 1.0 V, 1.8 V and 3.3 V")),
    row(("mono", "BTN1"), ("old mono", "PTA-142 + R87, R88"), ("arrow", "−"), ("mono", "deleted"),
        ("", "Removed to buy back board area &mdash; the button, its 10 k series resistor and its 10 k pull-down. "
             "Frees ball B18, which is now CHAN28 on header pin 41 &mdash; see §7. BTN is untouched")),
    row(("mono", "U10"), ("old", "— new —"), ("arrow", "＋"), ("mono", VAL["U10"]),
        ("", "FTDI reference-design EEPROM, carries the USB VID/PID/product string. <strong>16 bits wide</strong> "
             "&mdash; the <span class='mono'>B</span> suffix &mdash; because DS_FT2232H p27 requires it; see §3")),
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])

POWER = "".join([
    row(("mono", "VU / +5V"), ("", "X1 VBUS via D1, or VEXT via D2"), ("", "U8 input, X2 pin 36")),
    row(("mono", "VCC3V3"), ("", "U8 buck 3 + L3 (2.2 µH)"),
        ("", "%d pins &mdash; U1 VCCO on every bank, U3, X3, U2 VCCIO/VREGIN, U10, U4, J1, X2 pin 15" % len(NET["VCC3V3"]))),
    row(("mono", "VCC1V0"), ("", "U8 buck 1 + L1 (1.5 µH)"),
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        <thead><tr><th>Pin</th><th>Pad</th><th>MPSSE role</th><th>Net</th></tr></thead>
        <tbody>__CHA__</tbody></table></div>
      <p class="note">TCK/TDI/TDO/TMS are series-terminated through R89-R92 and shared with header JP3 and the R4 pack.
      GPIOL0/GPIOL1 carry <span class="mono">PROG#</span> and <span class="mono">DONE</span>, so the host can already
      force a reconfiguration and read back DONE without spending an FPGA general I/O.</p>
    </div>
    <div>
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    34.29, between CHAN3 and CHAN4. 10.16&nbsp;mm centre-to-centre, 8.64&nbsp;mm clear against X1's 7.80&nbsp;mm of
    copper and 7.50&nbsp;mm of body, so it clears both neighbours by 0.42&nbsp;mm. On the board that is
    <span class="mono">X1 at (22.90, 13.97) rot R90</span>, opening facing the x=25.40 edge.</li>
    <li><strong>Every pin keeps the signal it had.</strong> Pin 2 is still CHAN0, pin 5 still CHAN3, pin 6 still
    CHAN4, pin 13 still CHAN11 — the gate-to-pad map did not change. Only pads 2-5 moved, each +7.62&nbsp;mm into the
    space the gap had been occupying; pads 1 and 6-18 did not move at all.</li>
    <li><strong>The bottom row was closed up and is contiguous</strong> — pins 19..37 from x=49.53 down to x=3.81, and
    the empty position is the board corner at x=1.27. Getting there <strong>moved three pins</strong> 2.54 mm:
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    <li><strong>The gap is reserved, not spare.</strong> It is kept clear for the edge-mounted micro-USB. As drawn, X1
    needs 2.60 mm for its contacts and about 7.8 mm for its shell against 6.10 mm of clear space, so the board edge has
    to move out or a third position has to go before it drops in.</li>
    <li>Channels are now <span class="mono">CHAN0..CHAN27</span> on pins 2-13 and 19-34, contiguous. The old numbering
    ran 0-13 then 15-31 — there was never a CHAN14. GND is pin 16, and it is the only ground pin.</li>
    <li><strong>The board is now 0.800 &times; 2.750 in &mdash; 20.32 &times; 69.85&nbsp;mm &mdash; and sized to a
    breadboard.</strong> X2's two rows were 0.900&nbsp;in apart, which is columns B and I and leaves one free column
    each side. They are now <strong>0.700&nbsp;in</strong> apart: columns <strong>C and H</strong>, with A, B, I and J
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
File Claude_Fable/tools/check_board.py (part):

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        # found 107 where this file reported a clean board: 93 of them the escape
        # ring at 0.390 mm pitch on 0.2 mm drills, which is 0.190 edge to edge
        # against mdDrill 0.200, and three of them SAME-NET vias sitting on top
        # of each other -- EN_BIAS at 0.010 mm apart, SW2_NET overlapping by
        # 0.048. A checker that reports 0 findings on that is worse than no
        # checker.
        for i in range(len(dlist)):
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        for nm, vx, vy, dia, lo, hi in vlist:
            for onet, px, py, r, side, hx, hy, cr, ri in cop:
                # A PAD WITH NO NET IS STILL COPPER. Skipping onet is None let
                # two CHAN15 vias sit on U2's unconnected pins 58 and 30 --
                # Fusion's "Overlap Smd-Via" and "Copper Clearance Smd-Via",
                # four errors this file called a clean board.
                if onet == nm or hx is None:
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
